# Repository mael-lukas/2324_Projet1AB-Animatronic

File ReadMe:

# Animatronic (Trouvez un nom qui parle et vendeur)
> Présentation du projet, cahier des charges, état de l'art, etc...
Et on va essayer de faire un animatronique, un oiseau mecanique. (Vous n'allez pas essayer, vous allez faire !)
Et ce dans le cadre du projet de première année de MR. Papazoglou

# Equipe
Membre de l'équipe : 
* Vincent Fernandes
* Maël Lukas
* Romane Ponthieu
* Marie Ceccaldi
* Sedrenn Labrousse
> Rajouter les liens vers vos linked in, github, etc...

# Journal de bord
> Déroulé séance par séance

## Séance 1
## Séance 2
## Séance 3
## Séance 4
## Séance 5
## Séance 6
## Séance 7
## Séance 8
## Séance 9
## Séance 10

# Livrables
## PCB
> Présentation du schéma (grandes lignes) + PCB

## Code
> Architecture de votre code

## Rendu final
> Video ici de votre projet

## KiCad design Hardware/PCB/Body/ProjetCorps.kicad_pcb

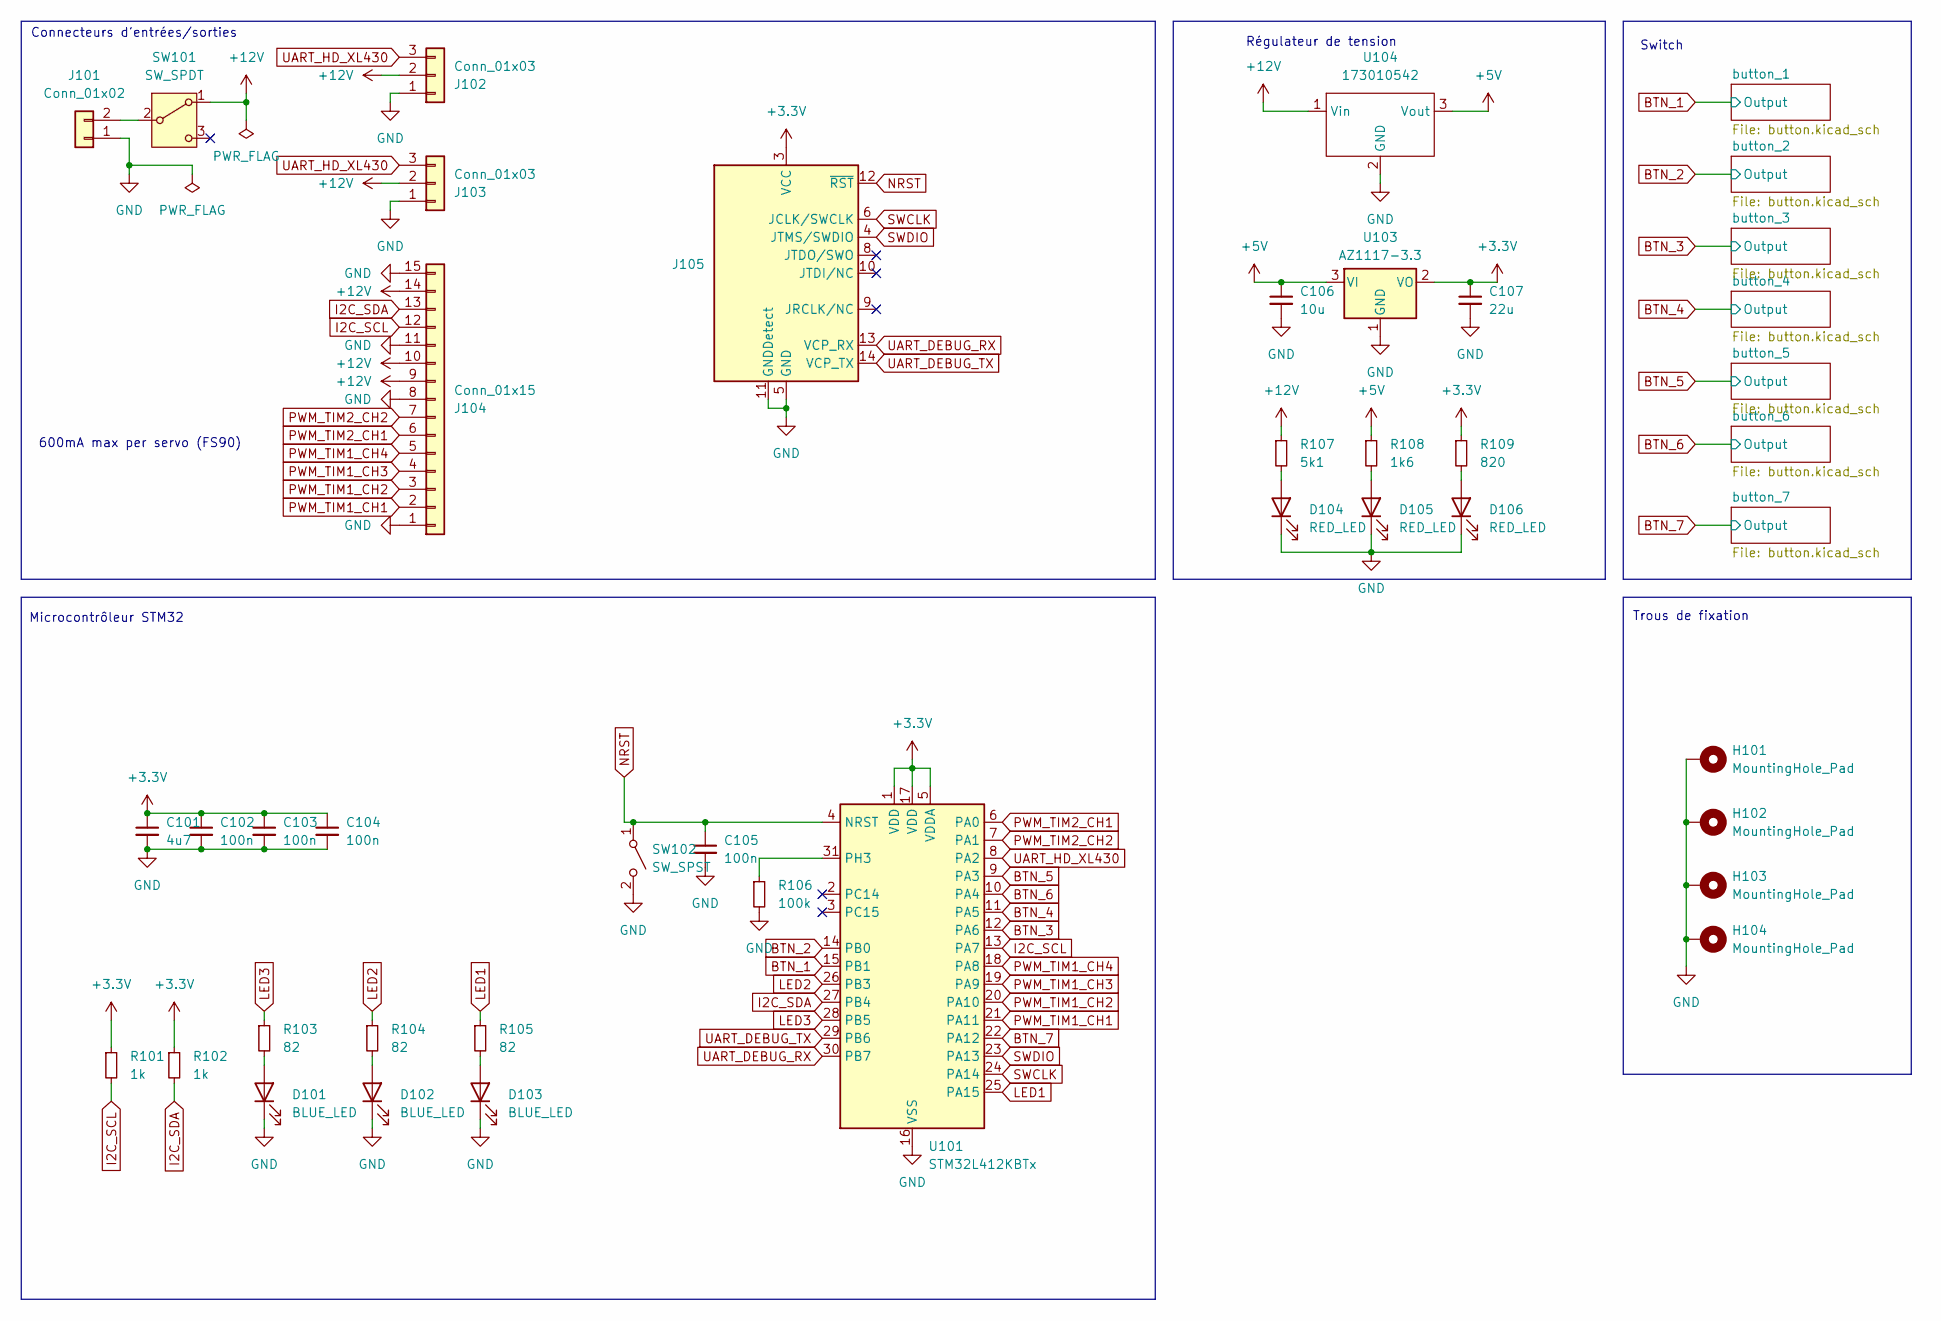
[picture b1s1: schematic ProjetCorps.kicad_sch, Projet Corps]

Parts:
C101: 4u7; C_0402_1005Metric
C102, C103, C104, C105: 100n; C_0402_1005Metric
C106: 10u; C_0402_1005Metric
C107: 22u; C_Elec_5x5.4
D101, D102, D103: BLUE_LED; LED_0603_1608Metric; MPN 150060BS55040
D104, D105, D106: RED_LED; LED_0603_1608Metric; MPN 150060RS55040
H101, H102, H103, H104: MountingHole_Pad; MountingHole_3.2mm_M3_Pad_Via
J101: Conn_01x02; AMASS_XT60-M_1x02_P7.20mm_Vertical
J102, J103: Conn_01x03; JST_EH_B3B-EH-A_1x03_P2.50mm_Vertical
J104: Conn_01x15; CONN15_31321_WRE; MPN 618015231421
J105: Conn_ST_STDC14; PinHeader_2x07_P1.27mm_Vertical_SMD
R101, R102: 1k; R_0402_1005Metric
R103, R104, R105: 82; R_0402_1005Metric
R106: 100k; R_0402_1005Metric
R107: 5k1; R_0402_1005Metric
R108: 1k6; R_0402_1005Metric
R109: 820; R_0402_1005Metric
SW101: SW_SPDT; 472123010111; MPN 472123010111
SW102: SW_SPST; SW_Push_1P1T_NO_6x6mm_H9.5mm
U101: STM32L412KBTx; LQFP-32_7x7mm_P0.8mm
U103: AZ1117-3.3; SOT-223-3_TabPin2; MPN AZ1117CH2-3.3TRG1
U104: 173010542

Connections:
+3.3V: C101.1, C102.1, C103.1, C104.1, C107.1, J105.3 (VCC), R101.1, R102.1, R109.1, U101.1 (VDD), U101.5 (VDDA), U101.17 (VDD), U103.2 (VO); also elsewhere on the board
+5V: C106.1, R108.1, U103.3 (VI), U104.3 (Vout)
+12V: J102.2, J103.2, J104.9, J104.10, J104.14, R107.1, SW101.1 (A), U104.1 (Vin)
BTN_1: U101.15 (PB1); also elsewhere on the board
BTN_2: U101.14 (PB0); also elsewhere on the board
BTN_3: U101.12 (PA6); also elsewhere on the board
BTN_4: U101.11 (PA5); also elsewhere on the board
BTN_5: U101.9 (PA3); also elsewhere on the board
BTN_6: U101.10 (PA4); also elsewhere on the board
BTN_7: U101.22 (PA12); also elsewhere on the board
GND: C101.2, C102.2, C103.2, C104.2, C105.2, C106.2, C107.2, D101.1 (K), D102.1 (K), D103.1 (K), D104.1 (K), D105.1 (K), D106.1 (K), H101.1, H102.1, H103.1, H104.1, J101.1, J102.1, J103.1, J104.1, J104.8, J104.11, J104.15, J105.5 (GND), J105.7 (GND), J105.11 (GNDDetect), R106.2, SW102.2 (B), U101.16 (VSS), U101.32 (VSS), U103.1 (GND), U104.2 (GND); also elsewhere on the board
I2C_SCL: J104.12, R101.2, U101.13 (PA7)
I2C_SDA: J104.13, R102.2, U101.27 (PB4)
LED1: R105.1, U101.25 (PA15)
LED2: R104.1, U101.26 (PB3)
LED3: R103.1, U101.28 (PB5)
NRST: C105.1, J105.12 (~RST), SW102.1 (A), U101.4 (NRST)
unnamed: D101.2 (A), R103.2
unnamed: D102.2 (A), R104.2
unnamed: D103.2 (A), R105.2
unnamed: D104.2 (A), R107.2
unnamed: D105.2 (A), R108.2
unnamed: D106.2 (A), R109.2
unnamed: J101.2, SW101.2 (B)
unnamed: R106.1, U101.31 (PH3)
PWM_TIM1_CH1: J104.2, U101.21 (PA11)
PWM_TIM1_CH2: J104.3, U101.20 (PA10)
PWM_TIM1_CH3: J104.4, U101.19 (PA9)
PWM_TIM1_CH4: J104.5, U101.18 (PA8)
PWM_TIM2_CH1: J104.6, U101.6 (PA0)
PWM_TIM2_CH2: J104.7, U101.7 (PA1)
SWCLK: J105.6 (JCLK/SWCLK), U101.24 (PA14)
SWDIO: J105.4 (JTMS/SWDIO), U101.23 (PA13)
UART_DEBUG_RX: J105.13 (VCP_RX), U101.30 (PB7)
UART_DEBUG_TX: J105.14 (VCP_TX), U101.29 (PB6)
UART_HD_XL430: J102.3, J103.3, U101.8 (PA2)

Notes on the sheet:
600mA max per servo (FS90)
Microcontrôleur STM32
Switch
Connecteurs d'entrées/sorties
Trous de fixation
Régulateur de tension

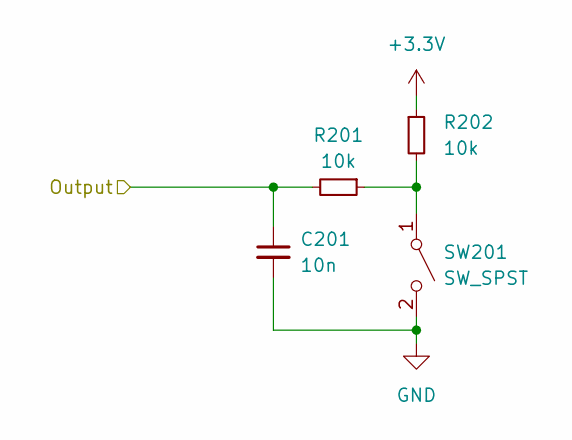
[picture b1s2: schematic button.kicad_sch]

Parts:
C201: 10n; C_0402_1005Metric
R201, R202: 10k; R_0402_1005Metric
SW201: SW_SPST; SW_Push_1P1T_NO_6x6mm_H9.5mm

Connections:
+3.3V: R202.1; also elsewhere on the board
BTN_6: C201.1, R201.2; also elsewhere on the board
GND: C201.2, SW201.2 (B); also elsewhere on the board
unnamed: R201.1, R202.2, SW201.1 (A)

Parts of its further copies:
C301, C401, C501, C601, C701, C801: 10n; C_0402_1005Metric
R301, R302, R401, R402, R501, R502, R601, R602, R701, R702, R801, R802: 10k; R_0402_1005Metric
SW301, SW401, SW501, SW601, SW701, SW801: SW_SPST; SW_Push_1P1T_NO_6x6mm_H9.5mm

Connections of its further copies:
+3.3V: R302.1, R402.1, R502.1, R602.1, R702.1, R802.1; also elsewhere on the board
BTN_1: C701.1, R701.2; also elsewhere on the board
BTN_2: C401.1, R401.2; also elsewhere on the board
BTN_3: C601.1, R601.2; also elsewhere on the board
BTN_4: C301.1, R301.2; also elsewhere on the board
BTN_5: C501.1, R501.2; also elsewhere on the board
BTN_7: C801.1, R801.2; also elsewhere on the board
GND: C301.2, C401.2, C501.2, C601.2, C701.2, C801.2, SW301.2 (B), SW401.2 (B), SW501.2 (B), SW601.2 (B), SW701.2 (B), SW801.2 (B); also elsewhere on the board
unnamed: R301.1, R302.2, SW301.1 (A)
unnamed: R401.1, R402.2, SW401.1 (A)
unnamed: R501.1, R502.2, SW501.1 (A)
unnamed: R601.1, R602.2, SW601.1 (A)
unnamed: R701.1, R702.2, SW701.1 (A)
unnamed: R801.1, R802.2, SW801.1 (A)

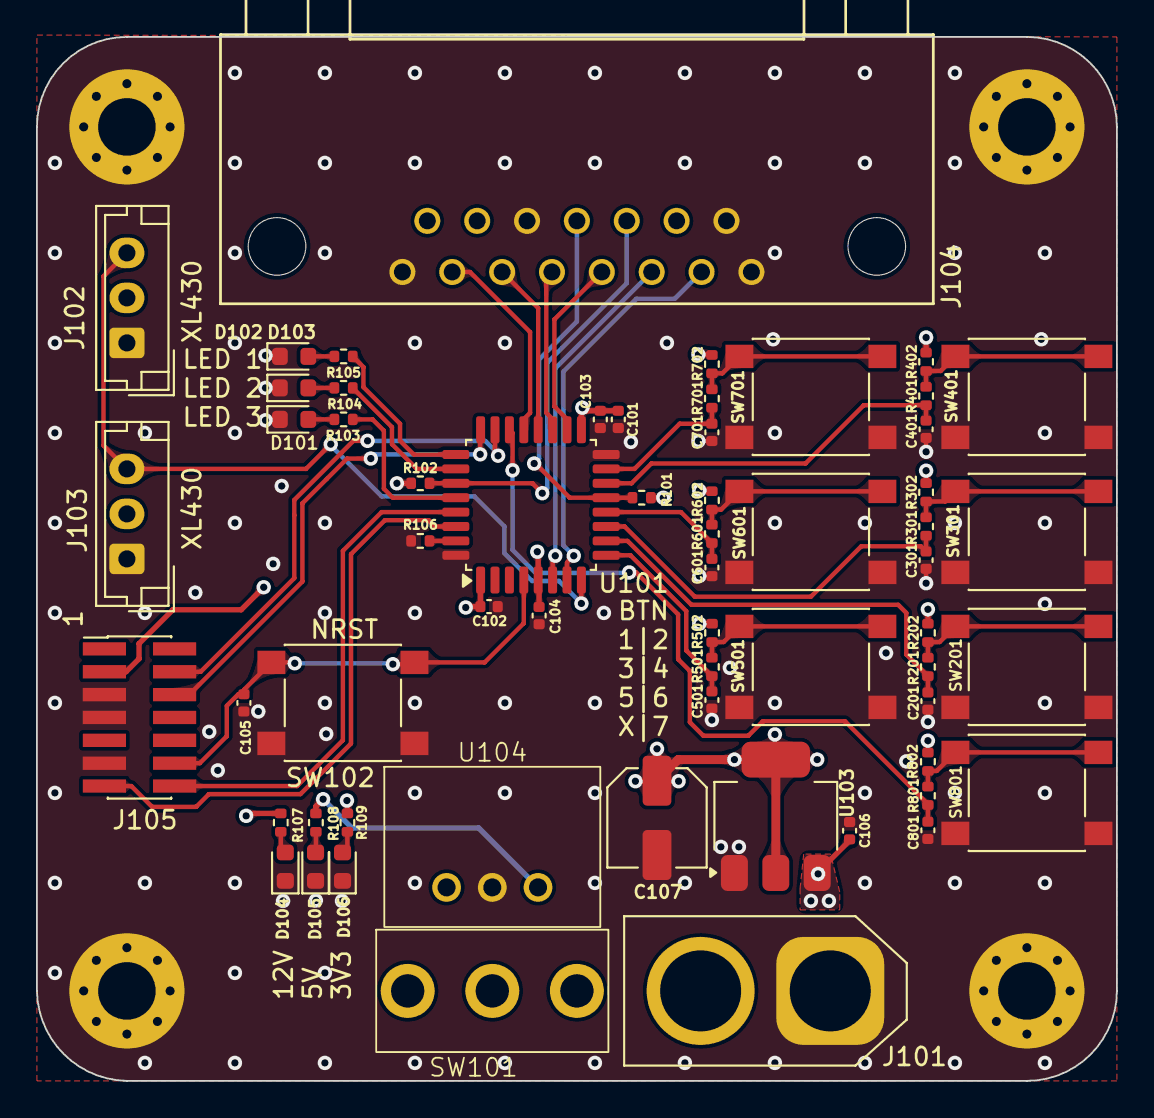
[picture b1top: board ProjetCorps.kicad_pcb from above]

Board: 4 copper layers, 60.0 x 58.0 mm, 64 parts (0 on the bottom side), 43 nets.

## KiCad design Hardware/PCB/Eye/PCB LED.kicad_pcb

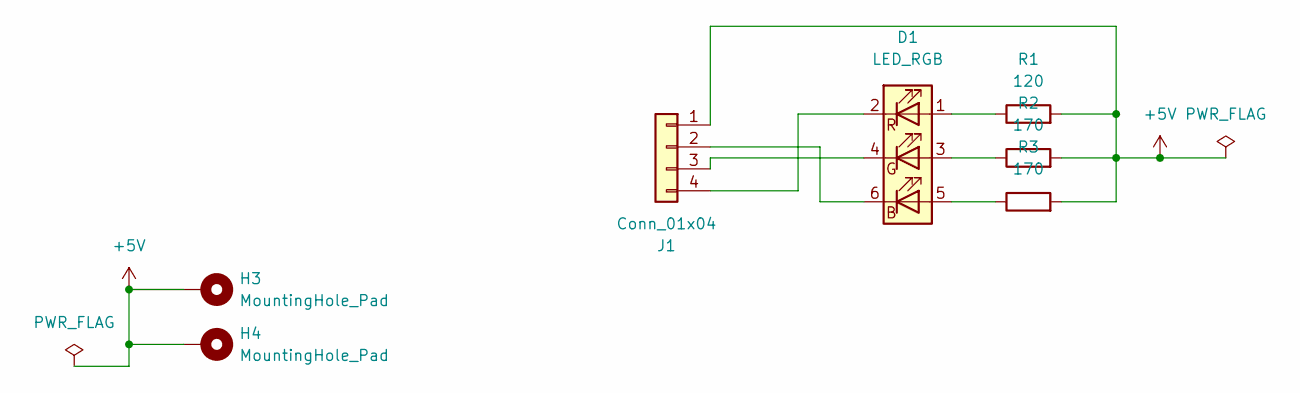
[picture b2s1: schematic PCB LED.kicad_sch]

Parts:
D1: LED_RGB; LED RGB
H3, H4: MountingHole_Pad; MountingHole_2.2mm_M2_Pad_Via
J1: Conn_01x04; JST_EH_B4B-EH-A_1x04_P2.50mm_Vertical
R1: 120; R_0402_1005Metric
R2, R3: 170; R_0402_1005Metric

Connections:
+5V: H3.1, H4.1, J1.1, R1.2, R2.2, R3.2
unnamed: D1.5 (BA), R3.1
unnamed: D1.6 (BK), J1.2
unnamed: D1.3 (GA), R2.1
unnamed: D1.4 (GK), J1.3
unnamed: D1.1 (RA), R1.1
unnamed: D1.2 (RK), J1.4

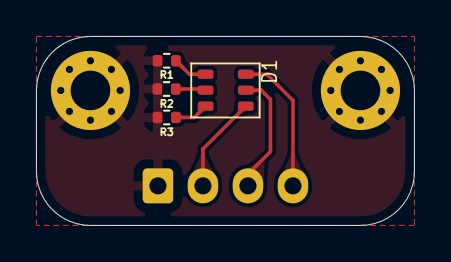
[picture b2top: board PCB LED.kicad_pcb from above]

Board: 2 copper layers, 21.0 x 10.5 mm, 7 parts (1 on the bottom side), 7 nets.

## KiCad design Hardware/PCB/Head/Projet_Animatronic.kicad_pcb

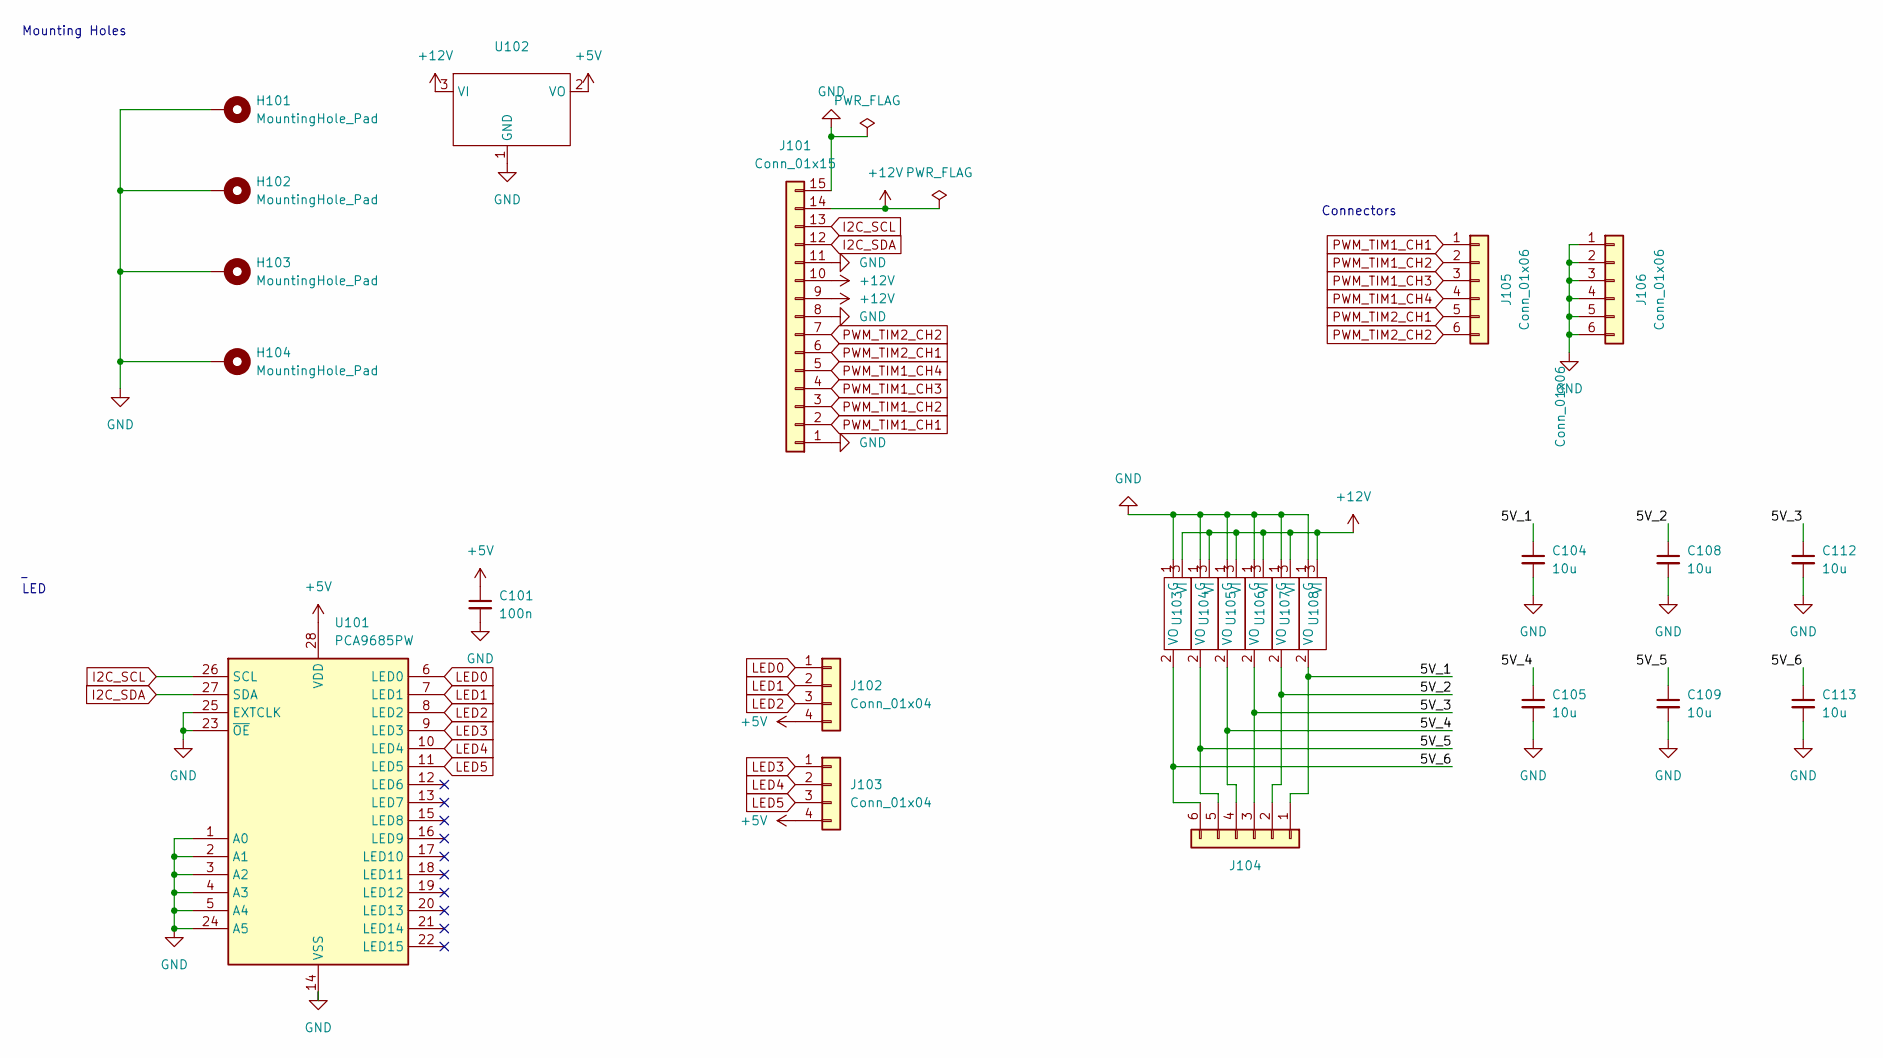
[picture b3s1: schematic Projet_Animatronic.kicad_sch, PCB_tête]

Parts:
C101: 100n; C_0402_1005Metric
C104, C105, C108, C109, C112, C113: 10u; C_0603_1608Metric
H101, H102, H103, H104: MountingHole_Pad; MountingHole_3.2mm_M3_Pad_Via
J101: Conn_01x15; CONN15_31321_WRE; MPN 618015231321
J102, J103: Conn_01x04; JST_XH_B4B-XH-A_1x04_P2.50mm_Vertical
J104, J105, J106: Conn_01x06; PinHeader_1x06_P2.54mm_Vertical
U101: PCA9685PW; TSSOP-28_4.4x9.7mm_P0.65mm
U102, U103, U104, U105, U106, U107, U108: 173010542

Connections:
+5V: C101.1, J102.4, J103.4, U101.28 (VDD), U102.2 (VO)
+12V: J101.9, J101.10, J101.14, U102.3 (VI), U103.3 (VI), U104.3 (VI), U105.3 (VI), U106.3 (VI), U107.3 (VI), U108.3 (VI)
/5V_1: C104.1, J104.1, U108.2 (VO)
/5V_2: C108.1, J104.2, U107.2 (VO)
/5V_3: C112.1, J104.3, U106.2 (VO)
/5V_4: C105.1, J104.4, U105.2 (VO)
/5V_5: C109.1, J104.5, U104.2 (VO)
/5V_6: C113.1, J104.6, U103.2 (VO)
GND: C101.2, C104.2, C105.2, C108.2, C109.2, C112.2, C113.2, H101.1, H102.1, H103.1, H104.1, J101.1, J101.8, J101.11, J101.15, J106.1, J106.2, J106.3, J106.4, J106.5, J106.6, U101.1 (A0), U101.2 (A1), U101.3 (A2), U101.4 (A3), U101.5 (A4), U101.14 (VSS), U101.23 (~OE), U101.24 (A5), U101.25 (EXTCLK), U102.1 (GND), U103.1 (G), U104.1 (G), U105.1 (G), U106.1 (G), U107.1 (G), U108.1 (G)
I2C_SCL: J101.13, U101.26 (SCL)
I2C_SDA: J101.12, U101.27 (SDA)
LED0: J102.1, U101.6 (LED0)
LED1: J102.2, U101.7 (LED1)
LED2: J102.3, U101.8 (LED2)
LED3: J103.1, U101.9 (LED3)
LED4: J103.2, U101.10 (LED4)
LED5: J103.3, U101.11 (LED5)
PWM_TIM1_CH1: J101.2, J105.1
PWM_TIM1_CH2: J101.3, J105.2
PWM_TIM1_CH3: J101.4, J105.3
PWM_TIM1_CH4: J101.5, J105.4
PWM_TIM2_CH1: J101.6, J105.5
PWM_TIM2_CH2: J101.7, J105.6

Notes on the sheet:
LED
Connectors
Mounting Holes

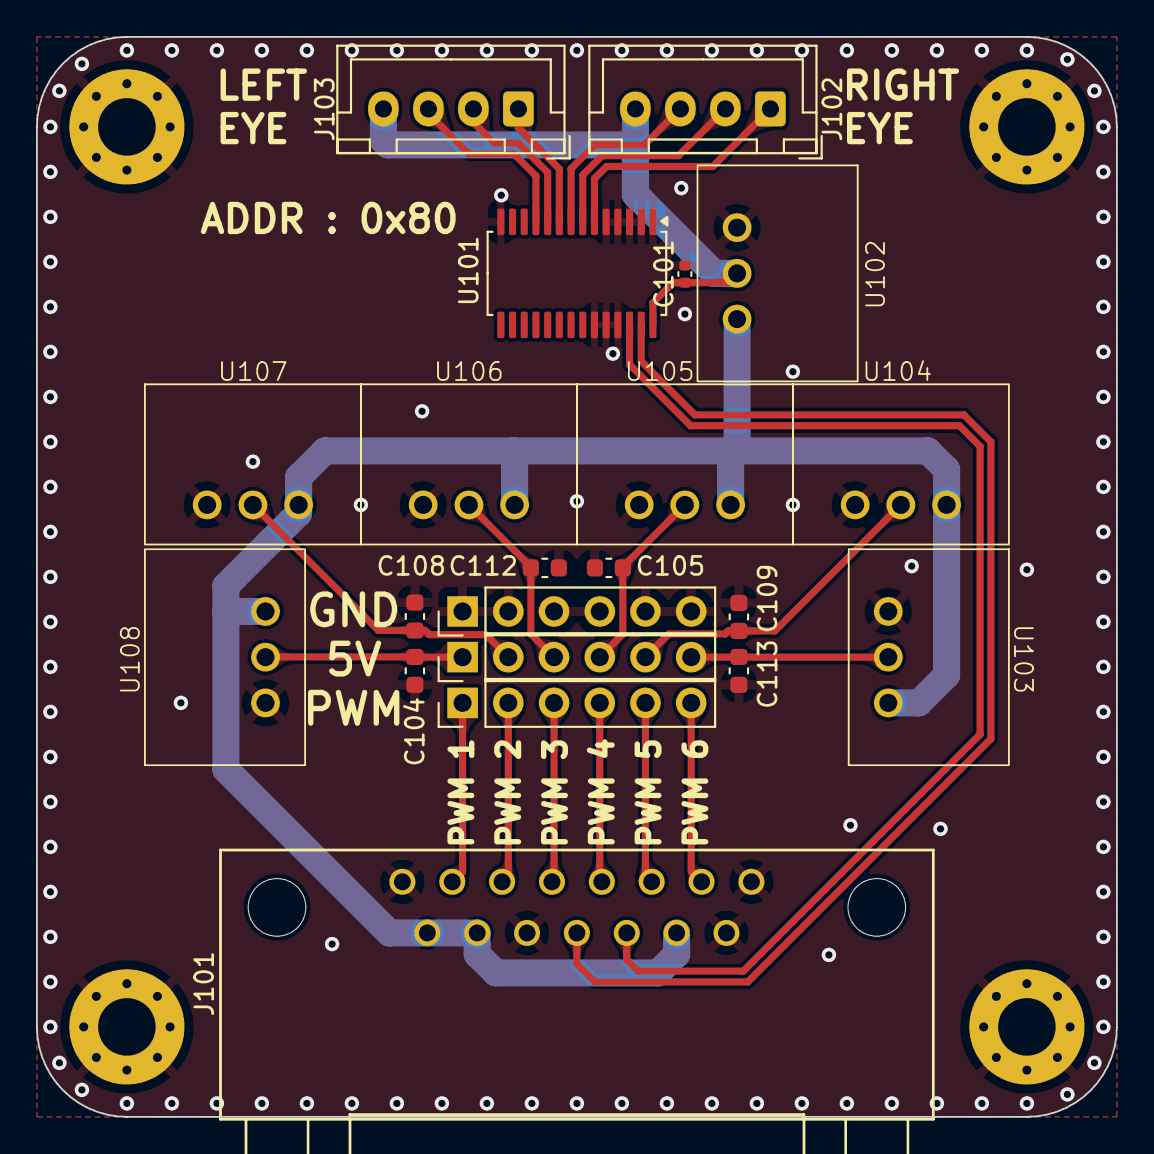
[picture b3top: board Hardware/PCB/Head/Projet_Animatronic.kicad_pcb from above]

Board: 2 copper layers, 60.0 x 60.0 mm, 25 parts (0 on the bottom side), 23 nets.

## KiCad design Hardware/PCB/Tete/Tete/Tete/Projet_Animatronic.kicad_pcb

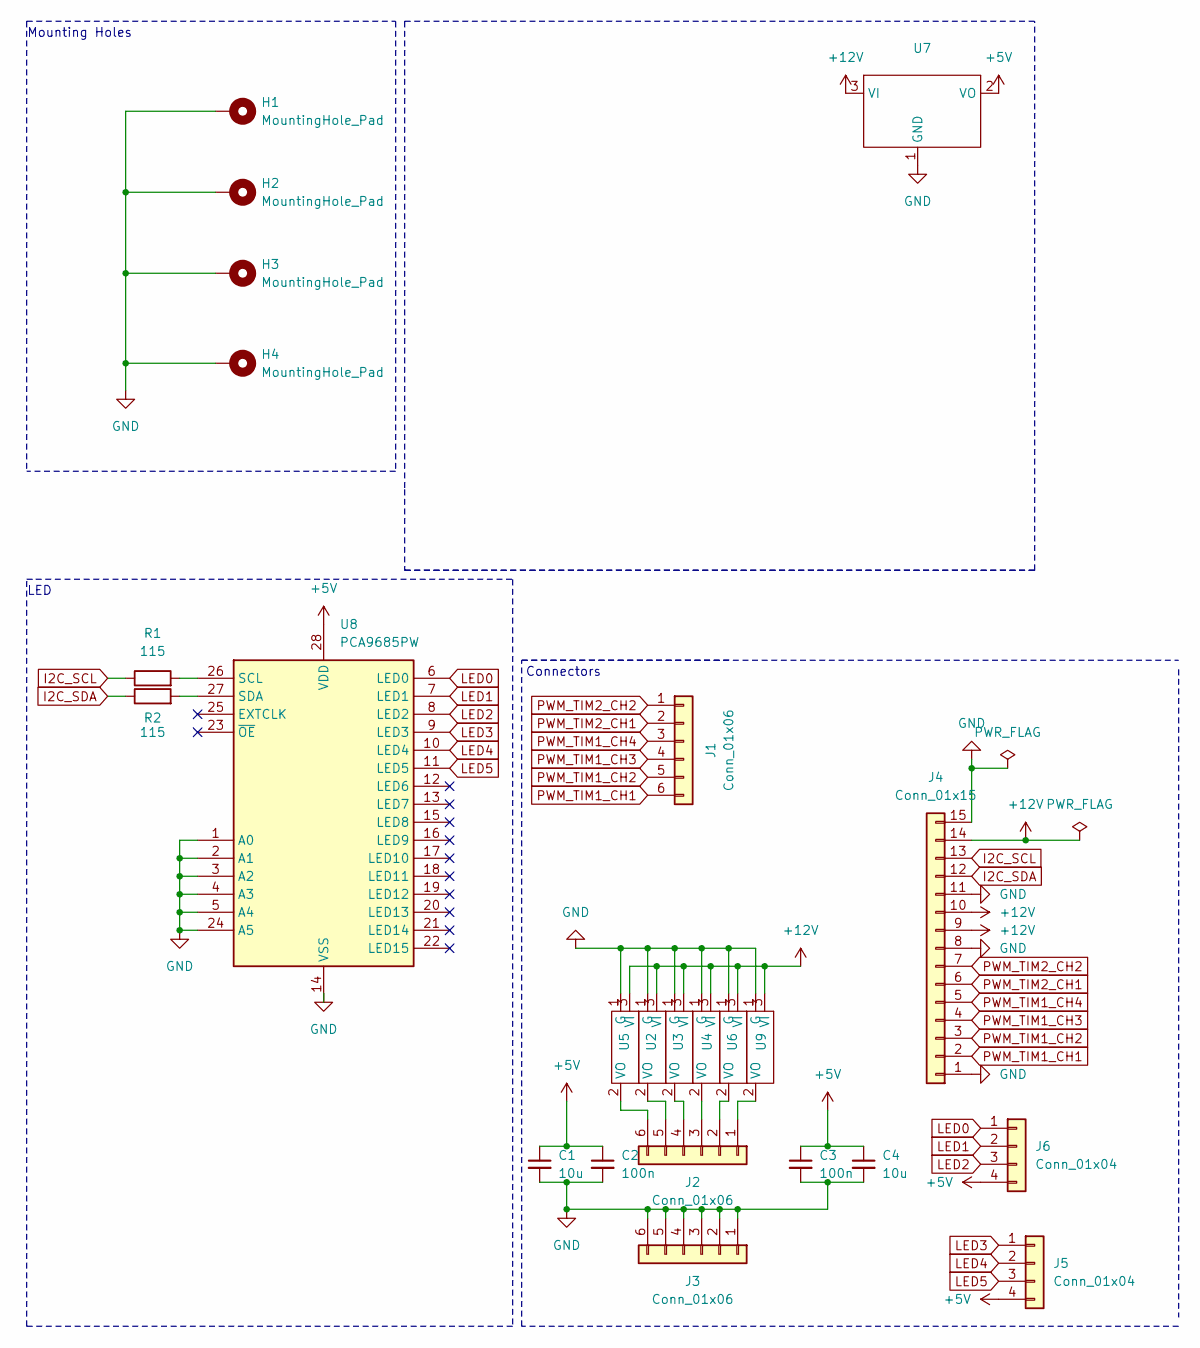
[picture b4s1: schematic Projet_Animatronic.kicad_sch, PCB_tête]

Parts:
C1, C4: 10u; C_0603_1608Metric_Pad1.08x0.95mm_HandSolder
C2, C3: 100n; C_0603_1608Metric_Pad1.08x0.95mm_HandSolder
H1, H2, H3, H4: MountingHole_Pad; MountingHole_3.2mm_M3_Pad_Via
J1, J2, J3: Conn_01x06; PinHeader_1x06_P2.54mm_Vertical
J4: Conn_01x15; CONN15_31321_WRE
J5, J6: Conn_01x04; PinHeader_1x04_P2.54mm_Vertical
R1, R2: 115; R_0603_1608Metric_Pad0.98x0.95mm_HandSolder
U2, U3, U4, U5, U6, U7, U9: 173010542
U8: PCA9685PW; TSSOP-28_4.4x9.7mm_P0.65mm

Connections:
+5V: C1.1, C2.1, C3.1, C4.1, J5.4, J6.4, U7.2 (VO), U8.28 (VDD)
+12V: J4.9, J4.10, J4.14, U2.3 (VI), U3.3 (VI), U4.3 (VI), U5.3 (VI), U6.3 (VI), U7.3 (VI), U9.3 (VI)
GND: C1.2, C2.2, C3.2, C4.2, H1.1, H2.1, H3.1, H4.1, J3.1, J3.2, J3.3, J3.4, J3.5, J3.6, J4.1, J4.8, J4.11, J4.15, U2.1 (G), U3.1 (G), U4.1 (G), U5.1 (G), U6.1 (G), U7.1 (GND), U8.1 (A0), U8.2 (A1), U8.3 (A2), U8.4 (A3), U8.5 (A4), U8.14 (VSS), U8.24 (A5), U9.1 (G)
I2C_SCL: J4.13, R1.1
I2C_SDA: J4.12, R2.1
LED0: J6.1, U8.6 (LED0)
LED1: J6.2, U8.7 (LED1)
LED2: J6.3, U8.8 (LED2)
LED3: J5.1, U8.9 (LED3)
LED4: J5.2, U8.10 (LED4)
LED5: J5.3, U8.11 (LED5)
unnamed: J2.1, U9.2 (VO)
unnamed: J2.2, U6.2 (VO)
unnamed: J2.3, U4.2 (VO)
unnamed: J2.4, U3.2 (VO)
unnamed: J2.5, U2.2 (VO)
unnamed: J2.6, U5.2 (VO)
unnamed: R1.2, U8.26 (SCL)
unnamed: R2.2, U8.27 (SDA)
PWM_TIM1_CH1: J1.6, J4.2
PWM_TIM1_CH2: J1.5, J4.3
PWM_TIM1_CH3: J1.4, J4.4
PWM_TIM1_CH4: J1.3, J4.5
PWM_TIM2_CH1: J1.2, J4.6
PWM_TIM2_CH2: J1.1, J4.7

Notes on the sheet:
LED
Connectors
Mounting Holes

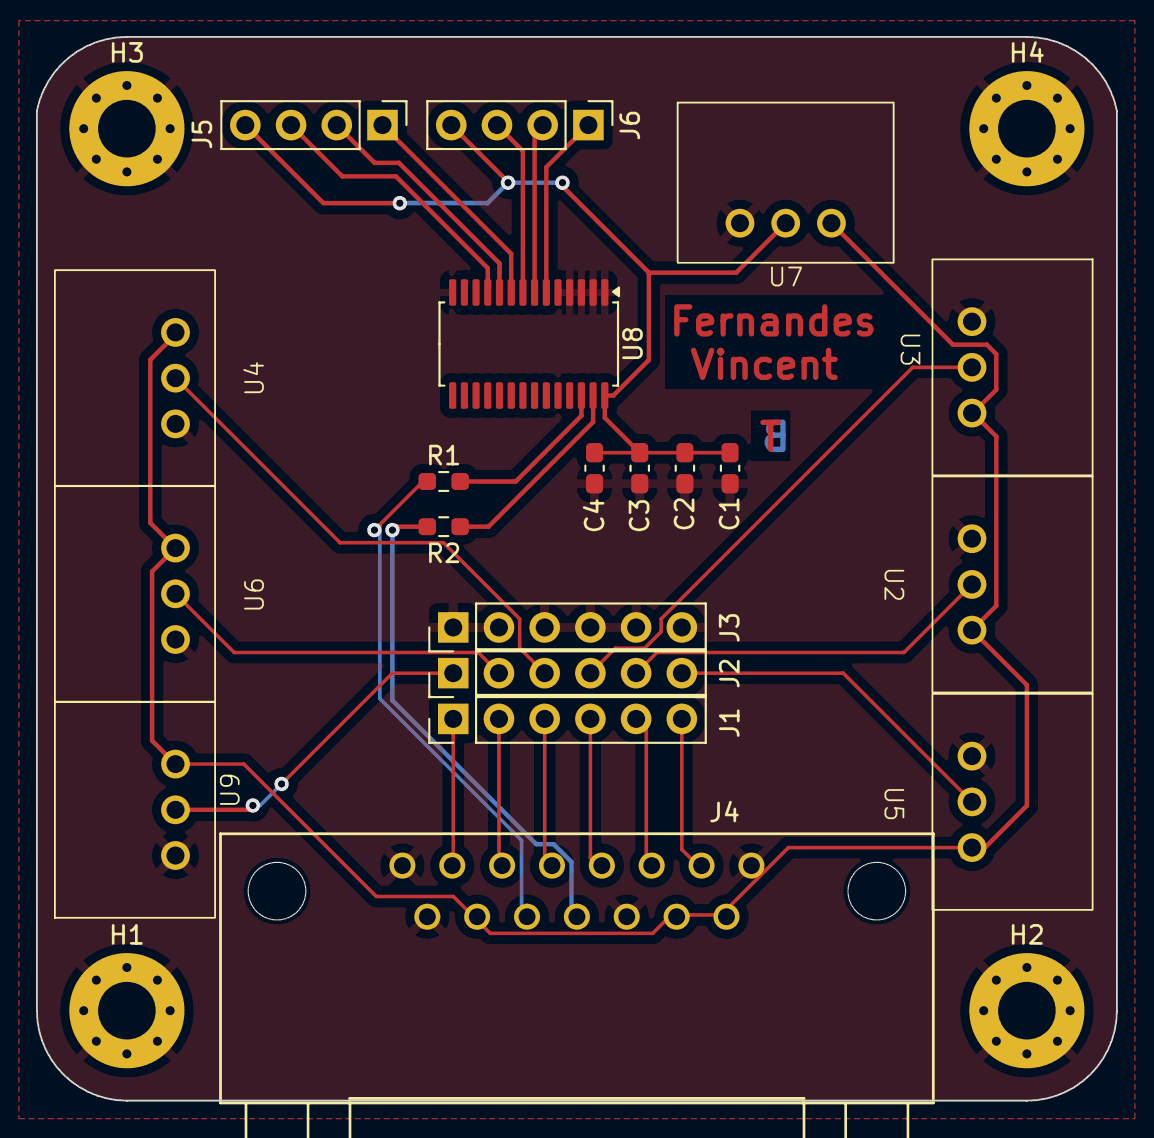
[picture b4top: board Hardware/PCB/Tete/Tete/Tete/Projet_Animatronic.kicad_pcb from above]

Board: 2 copper layers, 60.0 x 59.1 mm, 24 parts (0 on the bottom side), 25 nets.

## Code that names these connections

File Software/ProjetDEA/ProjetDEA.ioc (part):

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Mcu.Name=STM32L412KBTx
Mcu.Package=LQFP32
Mcu.UserName=STM32L412KBTx
PA0-CK_IN.Signal=S_TIM2_CH1
PA1.Signal=S_TIM2_CH2
PA10.Signal=S_TIM1_CH3
PA11.Signal=S_TIM1_CH4
PA12.GPIOParameters=GPIO_Label
PA12.GPIO_Label=BTN_7
PA12.Signal=GPIO_Input
PA13\ (JTMS/SWDIO).Mode=Serial_Wire
PA13\ (JTMS/SWDIO).Signal=SYS_JTMS-SWDIO
PA14\ (JTCK/SWCLK).Mode=Serial_Wire
PA14\ (JTCK/SWCLK).Signal=SYS_JTCK-SWCLK
PA15\ (JTDI).GPIOParameters=GPIO_Label
PA15\ (JTDI).GPIO_Label=LED1
PA15\ (JTDI).Signal=GPIO_Output
PA2.Mode=Half_duplex(single_wire_mode)
PA2.Signal=USART2_TX
PA3.GPIOParameters=GPIO_Label
PA3.GPIO_Label=BTN_6
PA3.Signal=GPIO_Input
PA4.GPIOParameters=GPIO_Label
PA4.GPIO_Label=BTN_5
PA4.Signal=GPIO_Input
PA5.GPIOParameters=GPIO_Label
PA5.GPIO_Label=BTN_4
PA5.Signal=GPIO_Input
PA6.GPIOParameters=GPIO_Label
PA6.GPIO_Label=BTN_3
PA6.Signal=GPIO_Input
PA7.Mode=I2C
PA7.Signal=I2C3_SCL
PA8.Signal=S_TIM1_CH1
PA9.Signal=S_TIM1_CH2
PB0.GPIOParameters=GPIO_Label
PB0.GPIO_Label=BTN_2
PB0.Signal=GPIO_Input
PB1.GPIOParameters=GPIO_Label
PB1.GPIO_Label=BTN_1
PB1.Signal=GPIO_Input
PB3\ (JTDO/TRACESWO).GPIOParameters=GPIO_Label
PB3\ (JTDO/TRACESWO).GPIO_Label=LED2
PB3\ (JTDO/TRACESWO).Signal=GPIO_Output
PB4\ (NJTRST).Mode=I2C
PB4\ (NJTRST).Signal=I2C3_SDA
PB5.GPIOParameters=GPIO_Label
PB5.GPIO_Label=LED3
PB5.Signal=GPIO_Output
PB6.Mode=Asynchronous
PB6.Signal=USART1_TX
PB7.Mode=Asynchronous
PB7.Signal=USART1_RX
RCC.HSE_VALUE=8000000
board=custom

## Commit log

2024-02-26 Create placeholder
2024-02-26 Create test
2024-02-26 diagramme d'architecture en cours
2024-02-26 Cahier des charges fonctionnel en cours
2024-02-27 Rename diagramme d'arcitecture animatronic.pdf to diagramme d'architecture animatronic.pdf
2024-02-27 Create modele 3D
2024-02-27 Create comparatif
2024-02-27 Update comparatif
2024-03-04 Create composants
2024-03-04 Rename composants to achats composants
2024-03-04 Ajouté(e) Diagramme sans nom.drawio
2024-03-04 Rename Diagramme sans nom.drawio to Elec Diag.drawio
2024-03-04 Datasheet buck
2024-03-04 datasheet STM32L412KBT6
2024-03-04 Moteur XL430-W250-T
2024-03-04 LED Driver
2024-03-04 Régulateur de tension
2024-03-04 Rename Etudes ailes oiseaux.pdf to Etude oiseau /Etudes ailes oiseaux.pdf
2024-03-04 Liste matériel nécessaire
2024-03-11 schémas et empreintes composants PCB
    618015231421 == WR-DSUB 10.30 mm Male Angled PCB Connector w. Hex Screw
    5988G10313F == Dialight LED RGB
    618015231321 == WR-DSUB 10.30 mm Female Angled PCB Connector w. Hex Screw
2024-03-11 schematic 1st version mb
2024-03-18 changement pcb tete
2024-03-18 change i2c addr led driver conf
2024-03-25 Create t
2024-03-25 Create versionfin
2024-03-25 revue PCB
2024-03-26 update pcb
2024-03-28 update head pcb
2024-03-28 update eye
2024-03-28 Create jaaj
2024-03-31 export gerbers
2024-04-06 correct mistake body pcb
2024-04-21 Rename ReadMe to readme.md
2024-04-27 header files for XL430
2024-04-29 début du XL430.c
2024-04-29 cahier des charges maj
2024-04-30 added XL430.c
2024-04-30 maj diagramme d'architecture
2024-05-13 add screenshots
2024-05-13 MAJ code en C
2024-05-13 add GIF
2024-05-13 add screen cache
2024-05-13 add picture 3D model eagle
2024-05-26 code pour les mini servo fini
2024-05-26 maj cahier des charges
2024-05-28 cache de l'alim
2024-05-28 add picture cache
2024-05-28 add pic cache
2024-05-28 modélisation 3d tête de l'oiseau
2024-05-28 architecture du code cubeide
2024-05-29 arrangement des pj
2024-05-29 add finalf
